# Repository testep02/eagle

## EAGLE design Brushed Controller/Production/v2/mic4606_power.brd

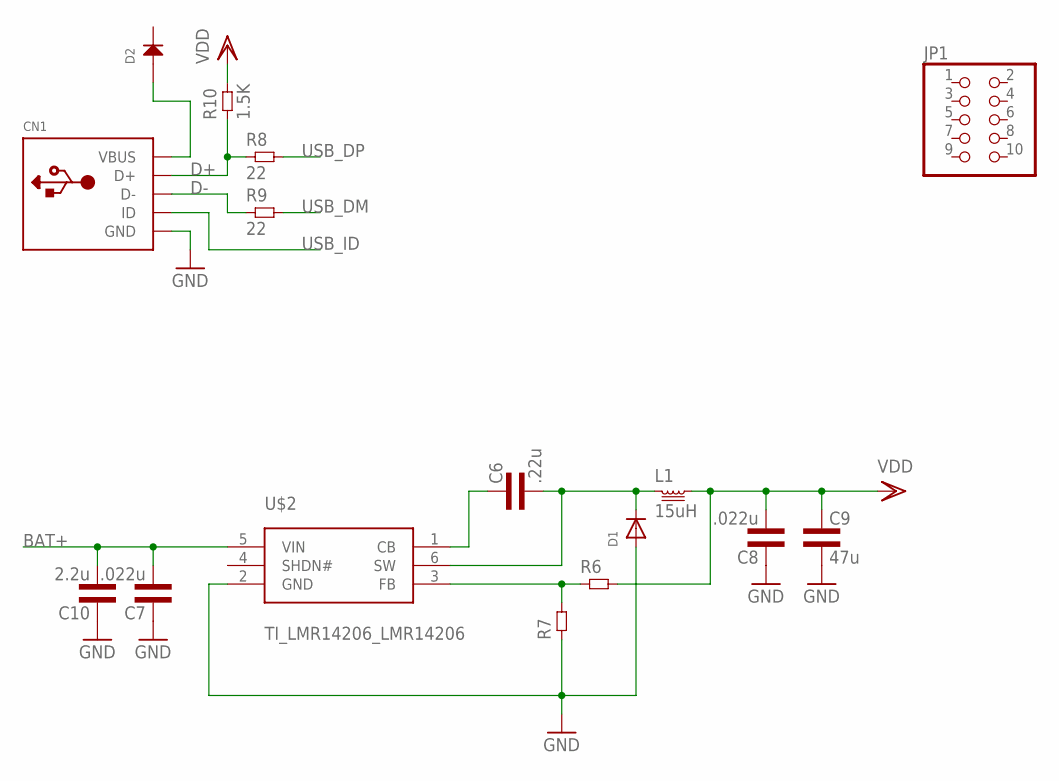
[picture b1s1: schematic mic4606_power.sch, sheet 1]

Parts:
C6: .22u; 0603L3
C7, C8: .022u; 0603L3
C9: 47u; 1210L3
C10: 2.2u; 1210L3
CN1: USBMINIB; USB-MINIB
D1: ADAFRUIT_DIODESMA; ADAFRUIT_SMADIODE
D2: DIODEDO-214AC; DO-214AC
JP1: PINHD-2X5; 2X05
L1: 15uH; NR4026
R6, R7: RES0603L3; 0603L3
R8, R9: 22; 0402L3
R10: 1.5K; 0402L3
U$2: TI_LMR14206_LMR14206; TI_LMR14206_R-PDSO-G6

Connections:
BAT+: C7.P$2 (2), C10.P$2 (2), U$2.5 (VIN); also elsewhere on the board
CB: C6.P$1 (1), U$2.1 (CB)
D+: CN1.D+, R8.P$1 (1), R10.P$1 (1)
D-: CN1.D-, R9.P$1 (1)
FB: R6.P$1 (1), R7.P$2 (2), U$2.3 (FB)
GND: C7.P$1 (1), C8.P$1 (1), C9.P$2 (2), C10.P$1 (1), CN1.GND, D1.A, R7.P$1 (1), U$2.2 (GND); also elsewhere on the board
SW: C6.P$2 (2), D1.C, L1.E (1), U$2.6 (SW)
USB_DM: R9.P$2 (2); also elsewhere on the board
USB_DP: R8.P$2 (2); also elsewhere on the board
USB_ID: CN1.ID; also elsewhere on the board
VBUS: CN1.VBUS, D2.1 (ANODE)
VDD: C8.P$2 (2), C9.P$1 (1), L1.F (2), R6.P$2 (2), R10.P$2 (2); also elsewhere on the board

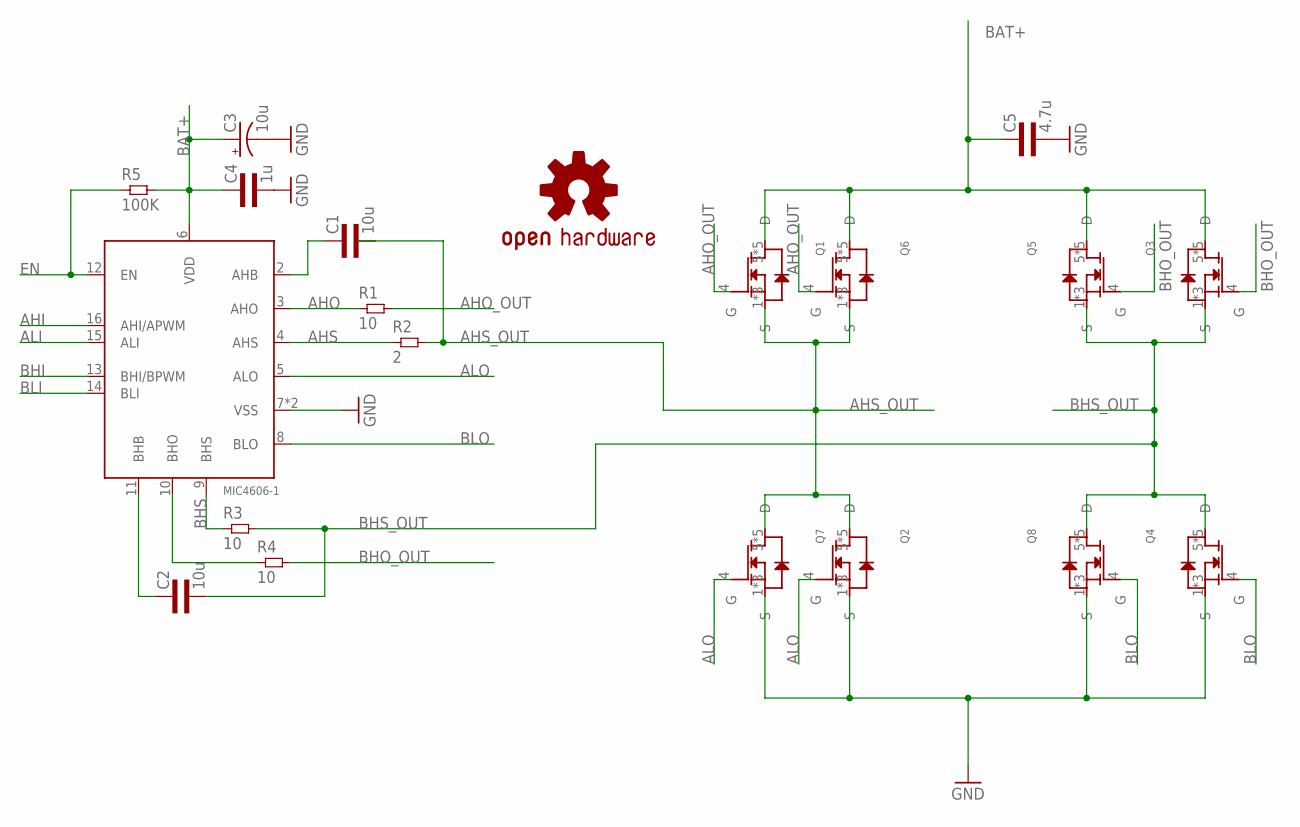
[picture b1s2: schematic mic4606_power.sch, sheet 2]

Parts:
C1, C2: 10u; 0805L3
C3: 10u; E1,8-4
C4: 1u; 0603L3
C5: 4.7u; 0805L3
LOGO1: OSHW-LOGOM; OSHW-LOGO-M
MD1: MIC4606-1; QFN44-16LD-PL-2
Q1, Q2, Q3, Q4, Q5, Q6, Q7, Q8: CSD18540Q5B; Q5B
R1, R3, R4: 10; 0805L3
R2: 2; 0805L3
R5: 100K; 0603L3

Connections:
AHI: MD1.16 (AHI/APWM)
AHO: MD1.3 (AHO), R1.1
AHO_OUT: Q1.4 (G), Q6.4 (G), R1.2
AHS: MD1.4 (AHS), R2.1
AHS_OUT: C1.2, Q1.1 (S), Q1.2 (S), Q1.3 (S), Q2.5 (D), Q2.6 (D), Q2.7 (D), Q2.8 (D), Q2.9 (D), Q6.1 (S), Q6.2 (S), Q6.3 (S), Q7.5 (D), Q7.6 (D), Q7.7 (D), Q7.8 (D), Q7.9 (D), R2.2
ALI: MD1.15 (ALI)
ALO: MD1.5 (ALO), Q2.4 (G), Q7.4 (G)
BAT+: C3.+, C4.P$1 (1), C5.1, MD1.6 (VDD), Q1.5 (D), Q1.6 (D), Q1.7 (D), Q1.8 (D), Q1.9 (D), Q3.5 (D), Q3.6 (D), Q3.7 (D), Q3.8 (D), Q3.9 (D), Q5.5 (D), Q5.6 (D), Q5.7 (D), Q5.8 (D), Q5.9 (D), Q6.5 (D), Q6.6 (D), Q6.7 (D), Q6.8 (D), Q6.9 (D), R5.P$2 (2); also elsewhere on the board
BHI: MD1.13 (BHI/BPWM)
BHO: MD1.10 (BHO), R4.1
BHO_OUT: Q3.4 (G), Q5.4 (G), R4.2
BHS: MD1.9 (BHS), R3.1
BHS_OUT: C2.2, Q3.1 (S), Q3.2 (S), Q3.3 (S), Q4.5 (D), Q4.6 (D), Q4.7 (D), Q4.8 (D), Q4.9 (D), Q5.1 (S), Q5.2 (S), Q5.3 (S), Q8.5 (D), Q8.6 (D), Q8.7 (D), Q8.8 (D), Q8.9 (D), R3.2
BLI: MD1.14 (BLI)
BLO: MD1.8 (BLO), Q4.4 (G), Q8.4 (G)
EN: MD1.12 (EN), R5.P$1 (1)
GND: C3.-, C4.P$2 (2), C5.2, MD1.7 (VSS), MD1.TP (VSS), Q2.1 (S), Q2.2 (S), Q2.3 (S), Q4.1 (S), Q4.2 (S), Q4.3 (S), Q7.1 (S), Q7.2 (S), Q7.3 (S), Q8.1 (S), Q8.2 (S), Q8.3 (S); also elsewhere on the board
unnamed: C1.1, MD1.2 (AHB)
unnamed: C2.1, MD1.11 (BHB)

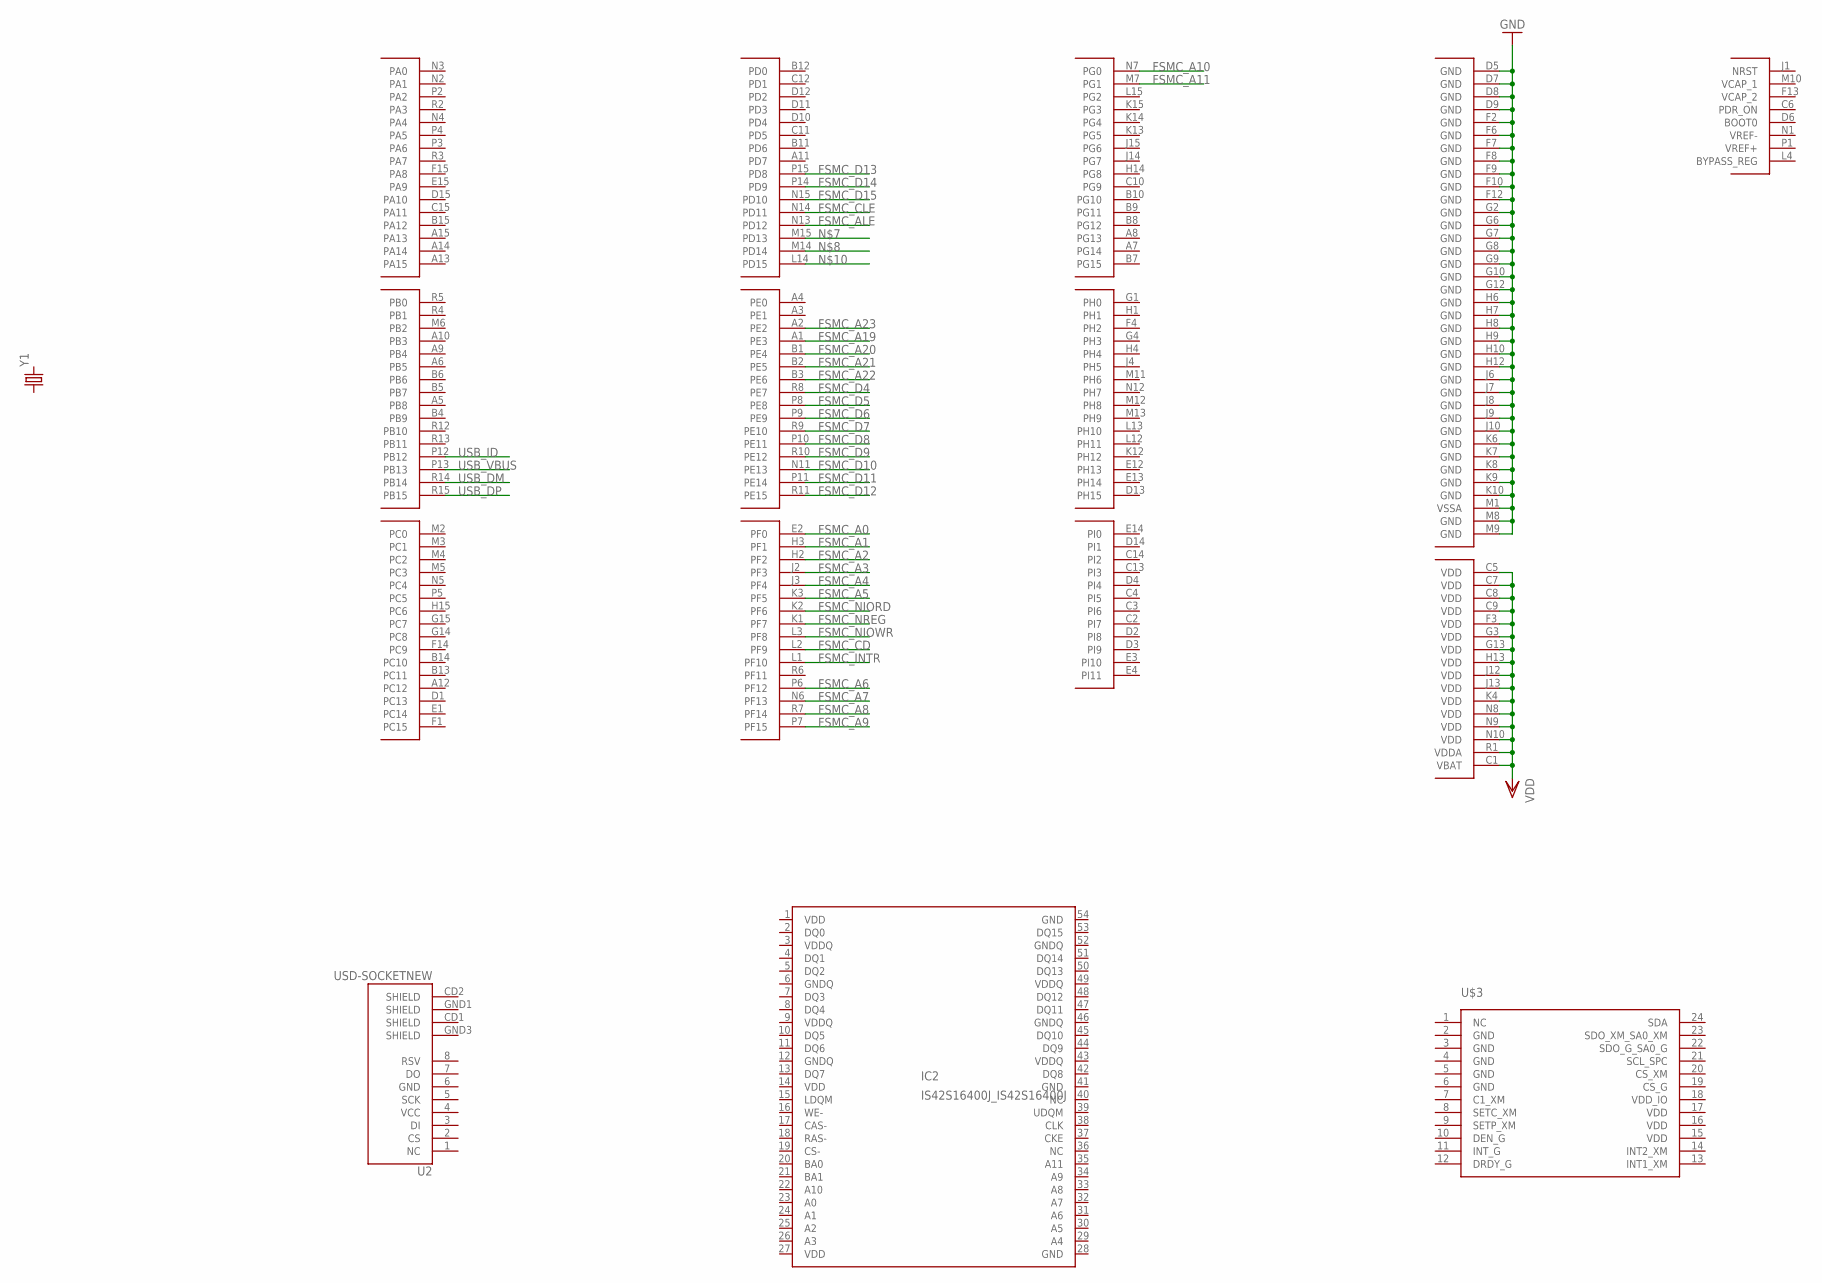
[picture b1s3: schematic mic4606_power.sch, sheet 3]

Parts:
IC2: IS42S16400J_IS42S16400J; IS42S16400J_TSOP-2
U2: USD-SOCKETNEW; MICRO-SD-SOCKET-PP
U$3: ST_LSM9DS0_TEMP_SENSE_LSM9DS0; ST_LSM9DS0_TEMP_SENSE_LGA-24
U$4: STM32_32BIT_MCU_STM32F407IG; STM32_32BIT_MCU_UFBGA176+25
Y1: CRYSTALHC49US; HC49US

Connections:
FSMC_A0: U$4.E2 (PF0)
FSMC_A1: U$4.H3 (PF1)
FSMC_A2: U$4.H2 (PF2)
FSMC_A3: U$4.J2 (PF3)
FSMC_A4: U$4.J3 (PF4)
FSMC_A5: U$4.K3 (PF5)
FSMC_A6: U$4.P6 (PF12)
FSMC_A7: U$4.N6 (PF13)
FSMC_A8: U$4.R7 (PF14)
FSMC_A9: U$4.P7 (PF15)
FSMC_A10: U$4.N7 (PG0)
FSMC_A11: U$4.M7 (PG1)
FSMC_A19: U$4.A1 (PE3)
FSMC_A20: U$4.B1 (PE4)
FSMC_A21: U$4.B2 (PE5)
FSMC_A22: U$4.B3 (PE6)
FSMC_A23: U$4.A2 (PE2)
FSMC_ALE: U$4.N13 (PD12)
FSMC_CD: U$4.L2 (PF9)
FSMC_CLE: U$4.N14 (PD11)
FSMC_D4: U$4.R8 (PE7)
FSMC_D5: U$4.P8 (PE8)
FSMC_D6: U$4.P9 (PE9)
FSMC_D7: U$4.R9 (PE10)
FSMC_D8: U$4.P10 (PE11)
FSMC_D9: U$4.R10 (PE12)
FSMC_D10: U$4.N11 (PE13)
FSMC_D11: U$4.P11 (PE14)
FSMC_D12: U$4.R11 (PE15)
FSMC_D13: U$4.P15 (PD8)
FSMC_D14: U$4.P14 (PD9)
FSMC_D15: U$4.N15 (PD10)
FSMC_INTR: U$4.L1 (PF10)
FSMC_NIORD: U$4.K2 (PF6)
FSMC_NIOWR: U$4.L3 (PF8)
FSMC_NREG: U$4.K1 (PF7)
GND: IC2.28 (GND), IC2.41 (GND), IC2.54 (GND), U$4.D5 (GND), U$4.D7 (GND), U$4.D8 (GND), U$4.D9 (GND), U$4.F2 (GND), U$4.F6 (GND), U$4.F7 (GND), U$4.F8 (GND), U$4.F9 (GND), U$4.F10 (GND), U$4.F12 (GND), U$4.G2 (GND), U$4.G6 (GND), U$4.G7 (GND), U$4.G8 (GND), U$4.G9 (GND), U$4.G10 (GND), U$4.G12 (GND), U$4.H6 (GND), U$4.H7 (GND), U$4.H8 (GND), U$4.H9 (GND), U$4.H10 (GND), U$4.H12 (GND), U$4.J6 (GND), U$4.J7 (GND), U$4.J8 (GND), U$4.J9 (GND), U$4.J10 (GND), U$4.K6 (GND), U$4.K7 (GND), U$4.K8 (GND), U$4.K9 (GND), U$4.K10 (GND), U$4.M1 (VSSA), U$4.M8 (GND), U$4.M9 (GND); also elsewhere on the board
GNDQ: IC2.6 (GNDQ), IC2.12 (GNDQ), IC2.46 (GNDQ), IC2.52 (GNDQ)
USB_DM: U$4.R14 (PB14); also elsewhere on the board
USB_DP: U$4.R15 (PB15); also elsewhere on the board
USB_ID: U$4.P12 (PB12); also elsewhere on the board
USB_VBUS: U$4.P13 (PB13)
VDD: IC2.1 (VDD), IC2.14 (VDD), IC2.27 (VDD), U$4.C1 (VBAT), U$4.C5 (VDD), U$4.C7 (VDD), U$4.C8 (VDD), U$4.C9 (VDD), U$4.F3 (VDD), U$4.G3 (VDD), U$4.G13 (VDD), U$4.H13 (VDD), U$4.J12 (VDD), U$4.J13 (VDD), U$4.K4 (VDD), U$4.N8 (VDD), U$4.N9 (VDD), U$4.N10 (VDD), U$4.R1 (VDDA); also elsewhere on the board
VDDQ: IC2.3 (VDDQ), IC2.9 (VDDQ), IC2.43 (VDDQ), IC2.49 (VDDQ)

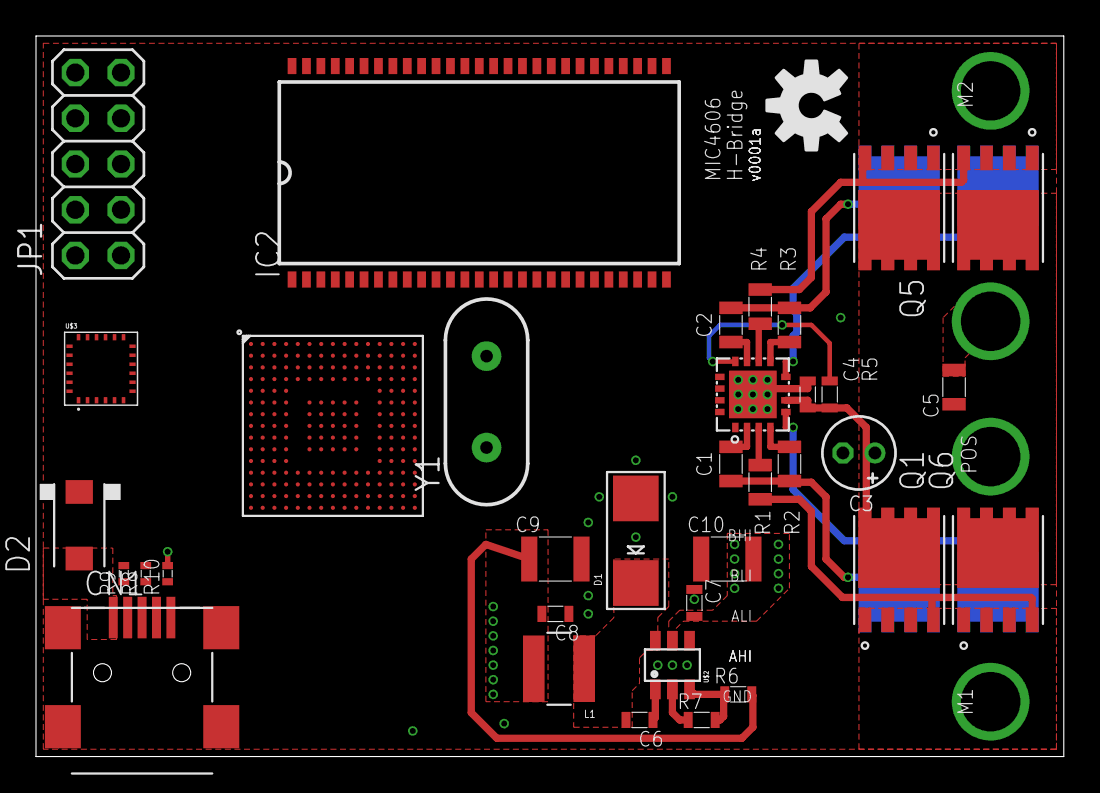
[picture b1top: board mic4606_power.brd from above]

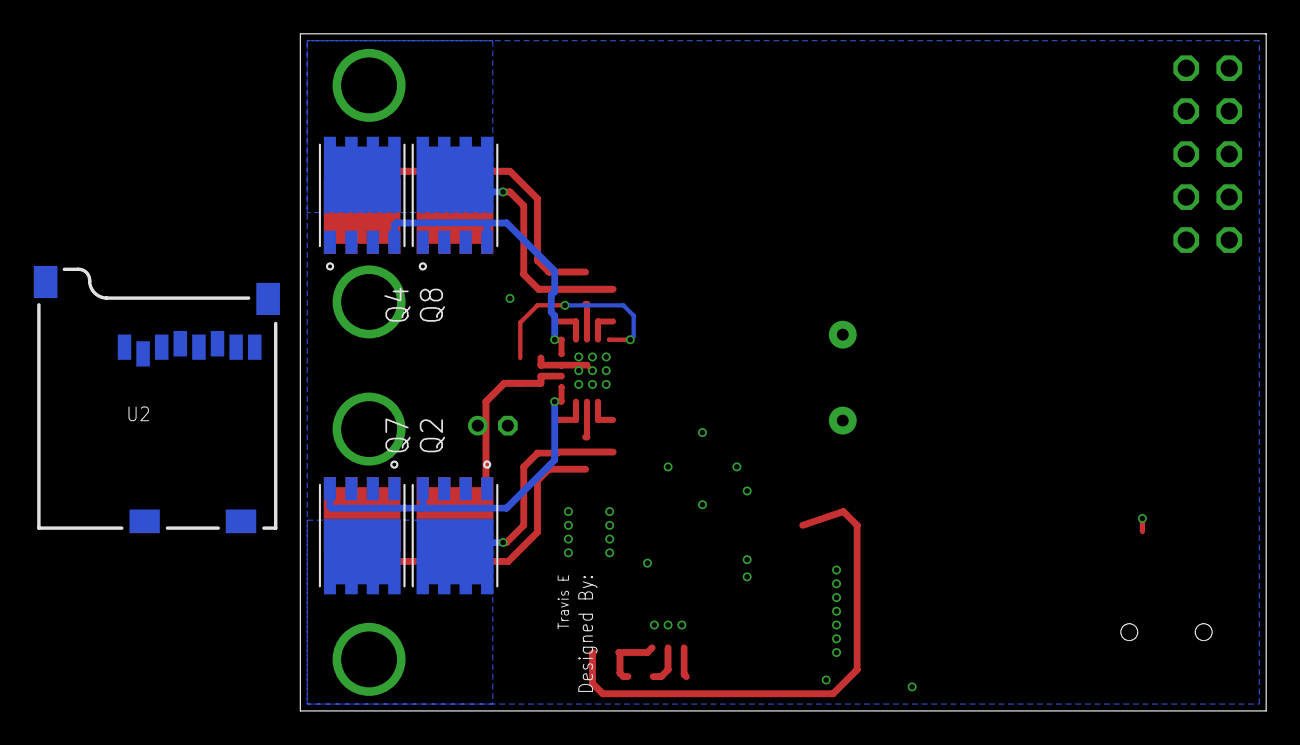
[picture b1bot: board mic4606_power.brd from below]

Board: 4 copper layers, 57.1 x 40.0 mm, 41 parts (5 on the bottom side), 27 nets.

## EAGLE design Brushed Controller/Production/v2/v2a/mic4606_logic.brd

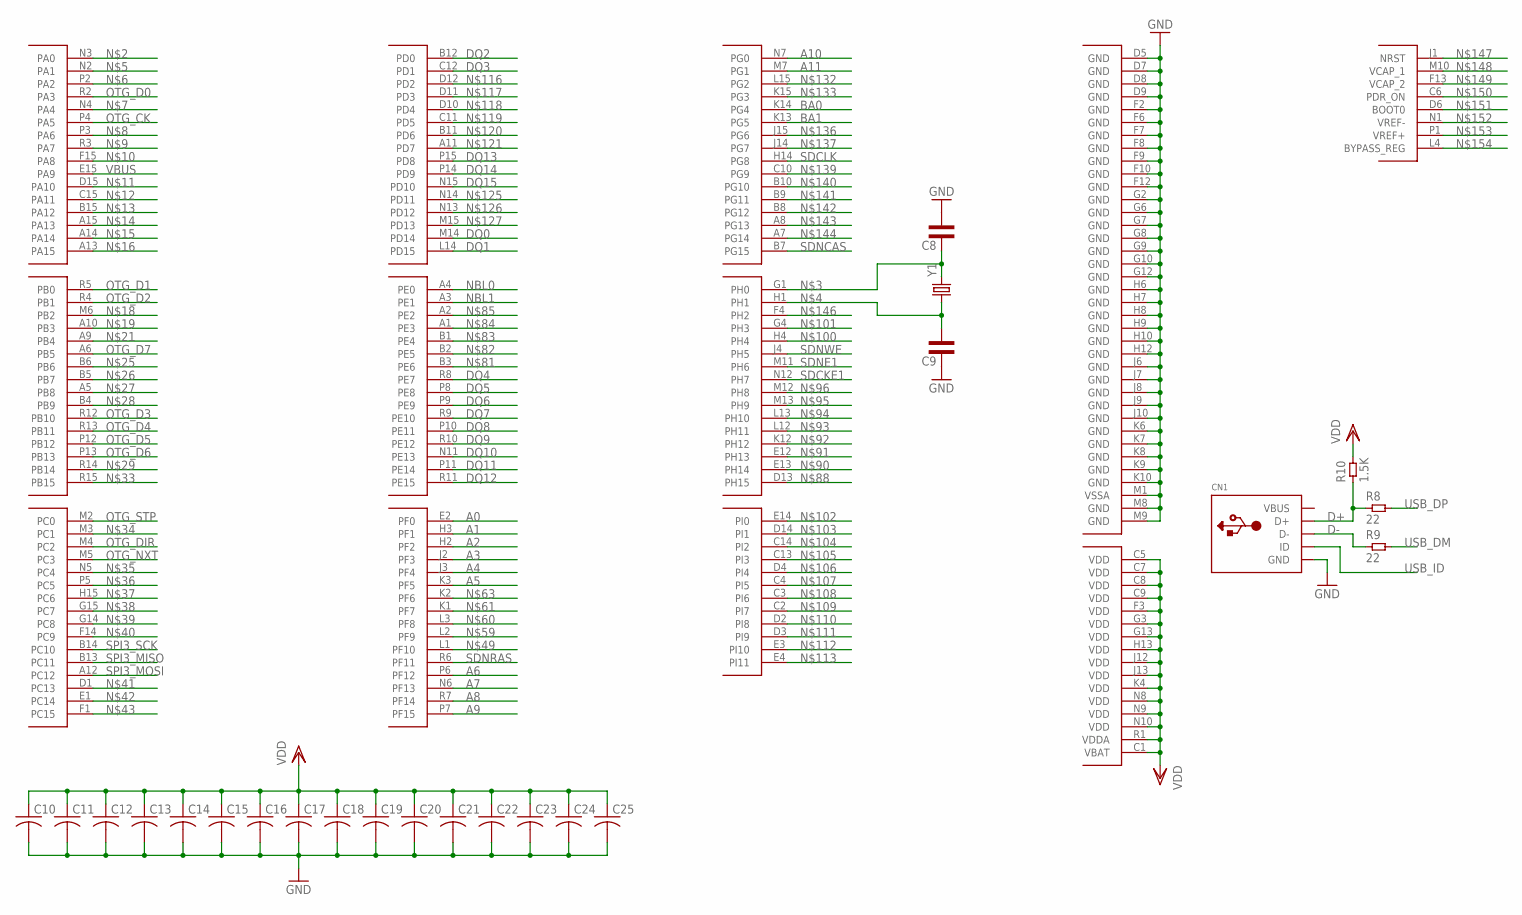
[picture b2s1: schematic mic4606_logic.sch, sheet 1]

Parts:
C8, C9: CAP0603L3; 0603L3
C10, C11, C12, C13, C14, C15, C16, C17, C18, C19, C20, C21, C22, C23, C24, C25: C-USC0201; C0201
CN1: USBMINIB; USB-MINIB
R8, R9: 22; 0402L3
R10: 1.5K; 0402L3
U$3: STM32_32BIT_MCU_STM32F407IG; STM32_32BIT_MCU_UFBGA176+25
Y1: CRYSTALHC49US; HC49US

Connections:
A0: U$3.E2 (PF0); also elsewhere on the board
A1: U$3.H3 (PF1); also elsewhere on the board
A2: U$3.H2 (PF2); also elsewhere on the board
A3: U$3.J2 (PF3); also elsewhere on the board
A4: U$3.J3 (PF4); also elsewhere on the board
A5: U$3.K3 (PF5); also elsewhere on the board
A6: U$3.P6 (PF12); also elsewhere on the board
A7: U$3.N6 (PF13); also elsewhere on the board
A8: U$3.R7 (PF14); also elsewhere on the board
A9: U$3.P7 (PF15); also elsewhere on the board
A10: U$3.N7 (PG0); also elsewhere on the board
A11: U$3.M7 (PG1); also elsewhere on the board
BA0: U$3.K14 (PG4); also elsewhere on the board
BA1: U$3.K13 (PG5); also elsewhere on the board
D+: CN1.D+, R8.P$1 (1), R10.P$1 (1)
D-: CN1.D-, R9.P$1 (1)
DQ0: U$3.M14 (PD14); also elsewhere on the board
DQ1: U$3.L14 (PD15); also elsewhere on the board
DQ2: U$3.B12 (PD0); also elsewhere on the board
DQ3: U$3.C12 (PD1); also elsewhere on the board
DQ4: U$3.R8 (PE7); also elsewhere on the board
DQ5: U$3.P8 (PE8); also elsewhere on the board
DQ6: U$3.P9 (PE9); also elsewhere on the board
DQ7: U$3.R9 (PE10); also elsewhere on the board
DQ8: U$3.P10 (PE11); also elsewhere on the board
DQ9: U$3.R10 (PE12); also elsewhere on the board
DQ10: U$3.N11 (PE13); also elsewhere on the board
DQ11: U$3.P11 (PE14); also elsewhere on the board
DQ12: U$3.R11 (PE15); also elsewhere on the board
DQ13: U$3.P15 (PD8); also elsewhere on the board
DQ14: U$3.P14 (PD9); also elsewhere on the board
DQ15: U$3.N15 (PD10); also elsewhere on the board
GND: C8.P$2 (2), C9.P$1 (1), C10.2, C11.2, C12.2, C13.2, C14.2, C15.2, C16.2, C17.2, C18.2, C19.2, C20.2, C21.2, C22.2, C23.2, C24.2, C25.2, CN1.GND, U$3.D5 (GND), U$3.D7 (GND), U$3.D8 (GND), U$3.D9 (GND), U$3.F2 (GND), U$3.F6 (GND), U$3.F7 (GND), U$3.F8 (GND), U$3.F9 (GND), U$3.F10 (GND), U$3.F12 (GND), U$3.G2 (GND), U$3.G6 (GND), U$3.G7 (GND), U$3.G8 (GND), U$3.G9 (GND), U$3.G10 (GND), U$3.G12 (GND), U$3.H6 (GND), U$3.H7 (GND), U$3.H8 (GND), U$3.H9 (GND), U$3.H10 (GND), U$3.H12 (GND), U$3.J6 (GND), U$3.J7 (GND), U$3.J8 (GND), U$3.J9 (GND), U$3.J10 (GND), U$3.K6 (GND), U$3.K7 (GND), U$3.K8 (GND), U$3.K9 (GND), U$3.K10 (GND), U$3.M1 (VSSA), U$3.M8 (GND), U$3.M9 (GND); also elsewhere on the board
unnamed: C8.P$1 (1), U$3.G1 (PH0), Y1.2
unnamed: C9.P$2 (2), U$3.H1, Y1.1
NBL0: U$3.A4 (PE0); also elsewhere on the board
NBL1: U$3.A3 (PE1); also elsewhere on the board
OTG_CK: U$3.P4 (PA5); also elsewhere on the board
OTG_D0: U$3.R2 (PA3); also elsewhere on the board
OTG_D1: U$3.R5 (PB0); also elsewhere on the board
OTG_D2: U$3.R4 (PB1); also elsewhere on the board
OTG_D3: U$3.R12 (PB10); also elsewhere on the board
OTG_D4: U$3.R13 (PB11); also elsewhere on the board
OTG_D5: U$3.P12 (PB12); also elsewhere on the board
OTG_D6: U$3.P13 (PB13); also elsewhere on the board
OTG_D7: U$3.A6 (PB5); also elsewhere on the board
OTG_DIR: U$3.M4 (PC2); also elsewhere on the board
OTG_NXT: U$3.M5 (PC3); also elsewhere on the board
OTG_STP: U$3.M2 (PC0); also elsewhere on the board
SDCKE1: U$3.N12 (PH7); also elsewhere on the board
SDCLK: U$3.H14 (PG8); also elsewhere on the board
SDNCAS: U$3.B7 (PG15); also elsewhere on the board
SDNE1: U$3.M11 (PH6); also elsewhere on the board
SDNRAS: U$3.R6 (PF11); also elsewhere on the board
SDNWE: U$3.J4 (PH5); also elsewhere on the board
SPI3_MISO: U$3.B13 (PC11); also elsewhere on the board
SPI3_MOSI: U$3.A12 (PC12); also elsewhere on the board
SPI3_SCK: U$3.B14 (PC10); also elsewhere on the board
USB_DM: R9.P$2 (2); also elsewhere on the board
USB_DP: R8.P$2 (2); also elsewhere on the board
USB_ID: CN1.ID; also elsewhere on the board
VBUS: CN1.VBUS, U$3.E15 (PA9)
VDD: C10.1, C11.1, C12.1, C13.1, C14.1, C15.1, C16.1, C17.1, C18.1, C19.1, C20.1, C21.1, C22.1, C23.1, C24.1, C25.1, R10.P$2 (2), U$3.C1 (VBAT), U$3.C5 (VDD), U$3.C7 (VDD), U$3.C8 (VDD), U$3.C9 (VDD), U$3.F3 (VDD), U$3.G3 (VDD), U$3.G13 (VDD), U$3.H13 (VDD), U$3.J12 (VDD), U$3.J13 (VDD), U$3.K4 (VDD), U$3.N8 (VDD), U$3.N9 (VDD), U$3.N10 (VDD), U$3.R1 (VDDA); also elsewhere on the board

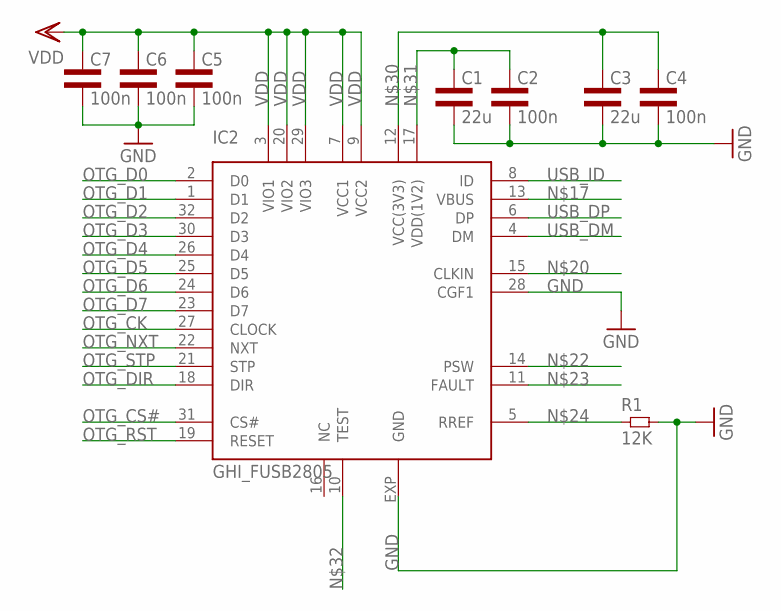
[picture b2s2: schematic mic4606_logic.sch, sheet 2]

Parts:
C1, C3: 22u; 0805L3
C2, C4, C5, C6, C7: 100n; 0603L3
IC2: GHI_FUSB2805; GHI_MLP32
R1: 12K; 0402L3

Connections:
GND: C1.2, C2.P$2 (2), C3.2, C4.P$2 (2), C5.P$2 (2), C6.P$2 (2), C7.P$2 (2), IC2.28 (CGF1), IC2.EXP (GND), R1.P$2 (2); also elsewhere on the board
unnamed: IC2.5 (RREF), R1.P$1 (1)
unnamed: C3.1, C4.P$1 (1), IC2.12 (VCC(3V3))
unnamed: C1.1, C2.P$1 (1), IC2.17 (VDD(1V2))
OTG_CK: IC2.27 (CLOCK); also elsewhere on the board
OTG_CS#: IC2.31 (CS#)
OTG_D0: IC2.2 (D0); also elsewhere on the board
OTG_D1: IC2.1 (D1); also elsewhere on the board
OTG_D2: IC2.32 (D2); also elsewhere on the board
OTG_D3: IC2.30 (D3); also elsewhere on the board
OTG_D4: IC2.26 (D4); also elsewhere on the board
OTG_D5: IC2.25 (D5); also elsewhere on the board
OTG_D6: IC2.24 (D6); also elsewhere on the board
OTG_D7: IC2.23 (D7); also elsewhere on the board
OTG_DIR: IC2.18 (DIR); also elsewhere on the board
OTG_NXT: IC2.22 (NXT); also elsewhere on the board
OTG_RST: IC2.19 (RESET)
OTG_STP: IC2.21 (STP); also elsewhere on the board
USB_DM: IC2.4 (DM); also elsewhere on the board
USB_DP: IC2.6 (DP); also elsewhere on the board
USB_ID: IC2.8 (ID); also elsewhere on the board
VDD: C5.P$1 (1), C6.P$1 (1), C7.P$1 (1), IC2.3 (VIO1), IC2.7 (VCC1), IC2.9 (VCC2), IC2.20 (VIO2), IC2.29 (VIO3); also elsewhere on the board

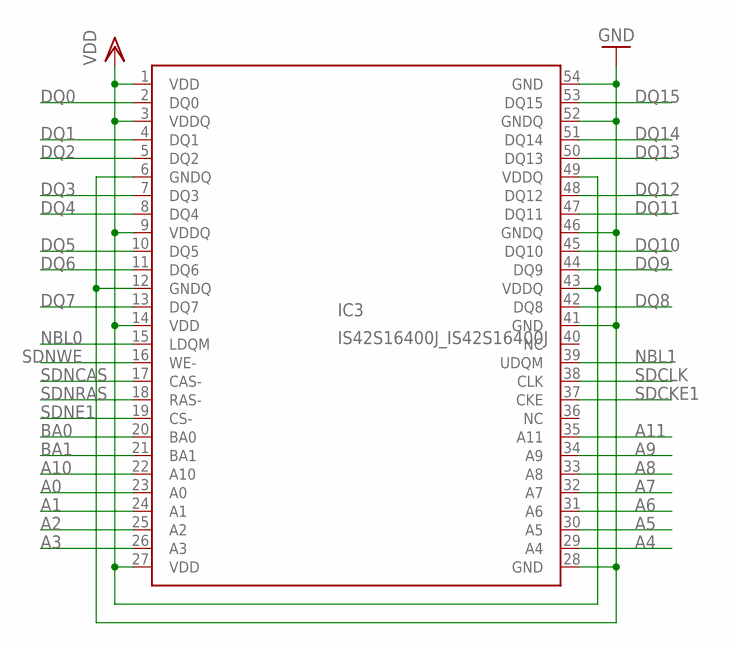
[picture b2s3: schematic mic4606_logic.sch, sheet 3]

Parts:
IC3: IS42S16400J_IS42S16400J; IS42S16400J_TSOP-2

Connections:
A0: IC3.23 (A0); also elsewhere on the board
A1: IC3.24 (A1); also elsewhere on the board
A2: IC3.25 (A2); also elsewhere on the board
A3: IC3.26 (A3); also elsewhere on the board
A4: IC3.29 (A4); also elsewhere on the board
A5: IC3.30 (A5); also elsewhere on the board
A6: IC3.31 (A6); also elsewhere on the board
A7: IC3.32 (A7); also elsewhere on the board
A8: IC3.33 (A8); also elsewhere on the board
A9: IC3.34 (A9); also elsewhere on the board
A10: IC3.22 (A10); also elsewhere on the board
A11: IC3.35 (A11); also elsewhere on the board
BA0: IC3.20 (BA0); also elsewhere on the board
BA1: IC3.21 (BA1); also elsewhere on the board
DQ0: IC3.2 (DQ0); also elsewhere on the board
DQ1: IC3.4 (DQ1); also elsewhere on the board
DQ2: IC3.5 (DQ2); also elsewhere on the board
DQ3: IC3.7 (DQ3); also elsewhere on the board
DQ4: IC3.8 (DQ4); also elsewhere on the board
DQ5: IC3.10 (DQ5); also elsewhere on the board
DQ6: IC3.11 (DQ6); also elsewhere on the board
DQ7: IC3.13 (DQ7); also elsewhere on the board
DQ8: IC3.42 (DQ8); also elsewhere on the board
DQ9: IC3.44 (DQ9); also elsewhere on the board
DQ10: IC3.45 (DQ10); also elsewhere on the board
DQ11: IC3.47 (DQ11); also elsewhere on the board
DQ12: IC3.48 (DQ12); also elsewhere on the board
DQ13: IC3.50 (DQ13); also elsewhere on the board
DQ14: IC3.51 (DQ14); also elsewhere on the board
DQ15: IC3.53 (DQ15); also elsewhere on the board
GND: IC3.6 (GNDQ), IC3.12 (GNDQ), IC3.28 (GND), IC3.41 (GND), IC3.46 (GNDQ), IC3.52 (GNDQ), IC3.54 (GND); also elsewhere on the board
NBL0: IC3.15 (LDQM); also elsewhere on the board
NBL1: IC3.39 (UDQM); also elsewhere on the board
SDCKE1: IC3.37 (CKE); also elsewhere on the board
SDCLK: IC3.38 (CLK); also elsewhere on the board
SDNCAS: IC3.17 (CAS-); also elsewhere on the board
SDNE1: IC3.19 (CS-); also elsewhere on the board
SDNRAS: IC3.18 (RAS-); also elsewhere on the board
SDNWE: IC3.16 (WE-); also elsewhere on the board
VDD: IC3.1 (VDD), IC3.3 (VDDQ), IC3.9 (VDDQ), IC3.14 (VDD), IC3.27 (VDD), IC3.43 (VDDQ), IC3.49 (VDDQ); also elsewhere on the board

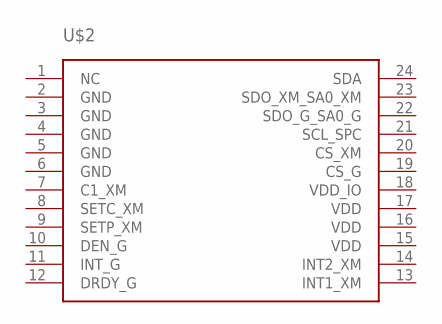
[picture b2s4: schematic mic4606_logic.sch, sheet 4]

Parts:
U$2: ST_LSM9DS0_TEMP_SENSE_LSM9DS0; ST_LSM9DS0_TEMP_SENSE_LGA-24

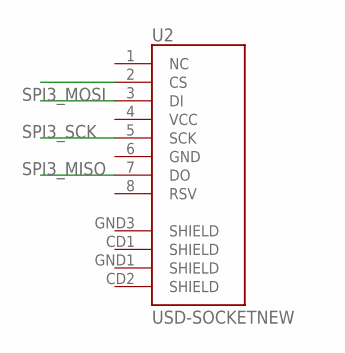
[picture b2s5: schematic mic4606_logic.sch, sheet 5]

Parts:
U2: USD-SOCKETNEW; MICRO-SD-SOCKET-PP

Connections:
SPI3_MISO: U2.7 (DO); also elsewhere on the board
SPI3_MOSI: U2.3 (DI); also elsewhere on the board
SPI3_SCK: U2.5 (SCK); also elsewhere on the board

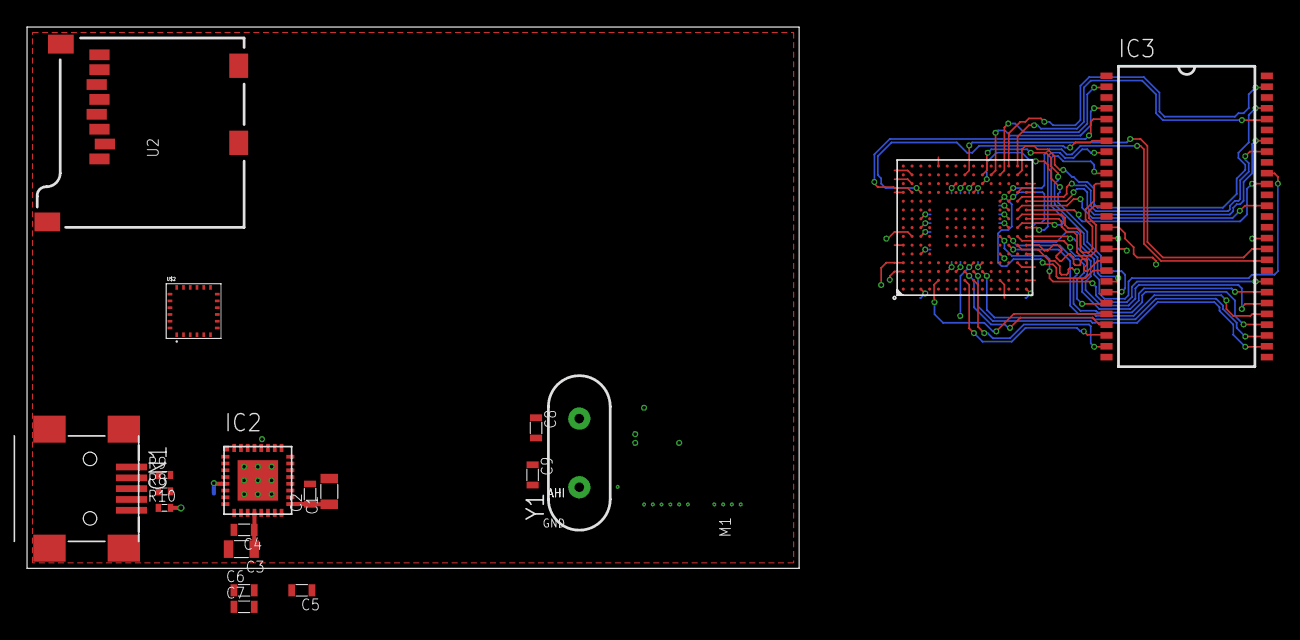
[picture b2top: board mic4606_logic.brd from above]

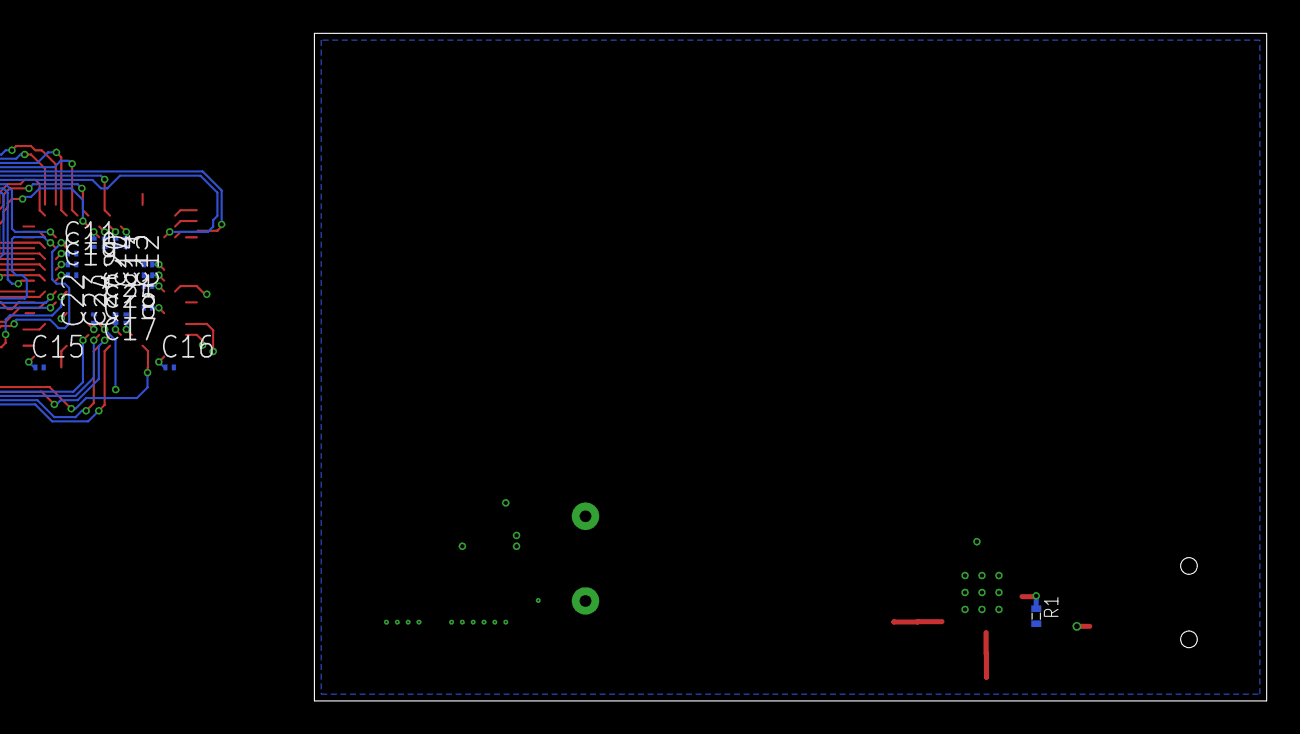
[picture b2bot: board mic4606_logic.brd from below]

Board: 4 copper layers, 57.1 x 40.0 mm, 36 parts (17 on the bottom side), 66 nets.

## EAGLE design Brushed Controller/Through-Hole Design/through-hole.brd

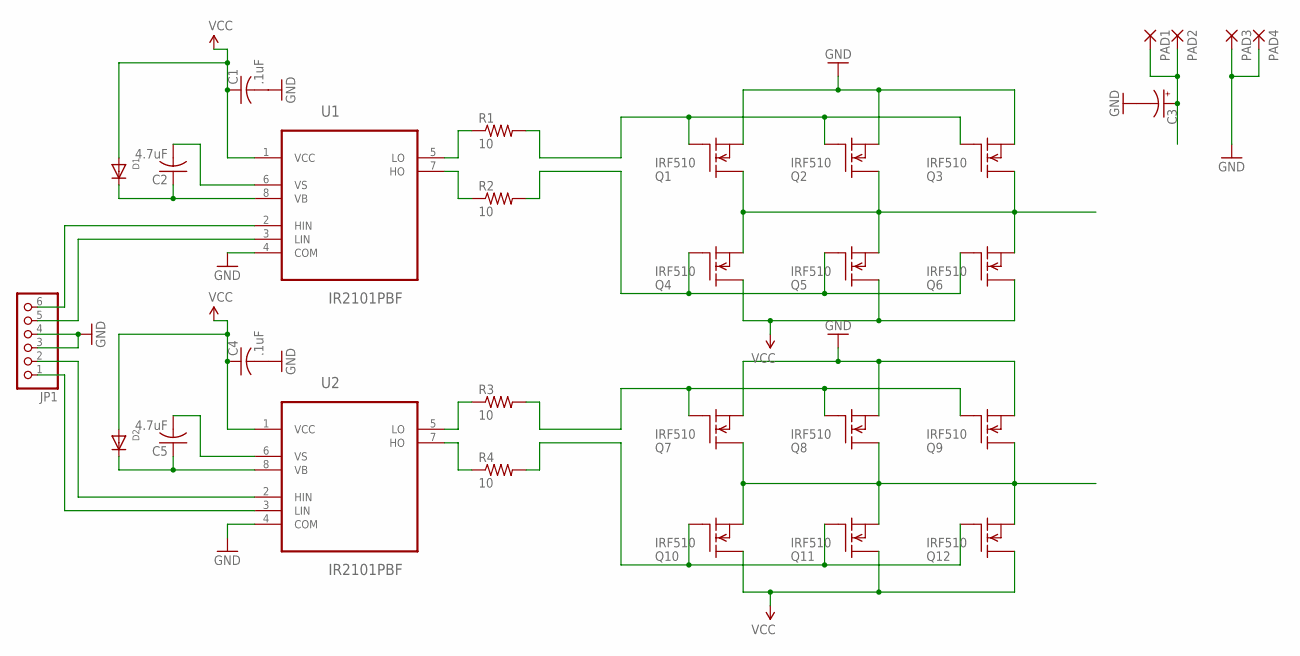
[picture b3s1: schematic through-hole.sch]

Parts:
C1, C4: .1uF; C0402K
C2, C5: 4.7uF; C0805K
C3: CPOL-USE5-10.5; E5-10,5
D1, D2: DIODESOD-323F; SOD-323F
JP1: PINHD-1X6; 1X06
PAD1, PAD2, PAD3, PAD4: 3,81/1,4
Q1, Q2, Q3, Q4, Q5, Q6, Q7, Q8, Q9, Q10, Q11, Q12: IRF510; TO220
R1, R2, R3, R4: 10; R0603
U1, U2: IR2101PBF; DIP254P762X533-8

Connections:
GND: C1.2, C3.-, C4.2, JP1.3, JP1.4, PAD3.1, PAD4.1, Q1.3 (S), Q2.3 (S), Q3.3 (S), Q7.3 (S), Q8.3 (S), Q9.3 (S), U1.4 (COM), U2.4 (COM)
MTR_OUT_1: Q1.2 (D), Q2.2 (D), Q3.2 (D), Q4.3 (S), Q5.3 (S), Q6.3 (S)
MTR_OUT_2: Q7.2 (D), Q8.2 (D), Q9.2 (D), Q10.3 (S), Q11.3 (S), Q12.3 (S)
unnamed: Q4.1 (G), Q5.1 (G), Q6.1 (G), R2.2
unnamed: Q1.1 (G), Q2.1 (G), Q3.1 (G), R1.2
unnamed: R3.1, U2.5 (LO)
unnamed: R4.1, U2.7 (HO)
unnamed: C2.1, D1.C, U1.8 (VB)
unnamed: C5.1, D2.C
unnamed: R1.1, U1.5 (LO)
unnamed: R2.1, U1.7 (HO)
unnamed: C2.2, U1.6 (VS)
unnamed: Q7.1 (G), Q8.1 (G), Q9.1 (G), R3.2
unnamed: JP1.1, U2.3 (LIN)
unnamed: Q10.1 (G), Q11.1 (G), Q12.1 (G), R4.2
unnamed: C3.+, PAD1.1, PAD2.1
unnamed: JP1.2, U2.2 (HIN)
unnamed: JP1.6, U1.2 (HIN)
unnamed: JP1.5, U1.3 (LIN)
VB: U2.8 (VB)
VCC: C1.1, C4.1, D1.A, D2.A, Q4.2 (D), Q5.2 (D), Q6.2 (D), Q10.2 (D), Q11.2 (D), Q12.2 (D), U1.1 (VCC), U2.1 (VCC)
VS: U2.6 (VS)

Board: 2 copper layers, 30 parts (0 on the bottom side), 20 nets, no tracks yet.

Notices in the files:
parts and their libraries:
SparkFun-Aesthetics: Licensing: CC v3.0 Share-Alike You are welcome to use this library for commercial purposes.
